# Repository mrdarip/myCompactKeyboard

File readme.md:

# my compact keyboard

## Description

## PCB
Here are pictures of my pcb:

| **Schematic** | **PCB** |
|---------------|---------|
|||

Hope it looks good to you!

[x] I ran DRC and there are 0 errors

## CAD
Designed two using OpenSCAD! I edited my previous macropad case for the keyboard

It's made to be 3D printed, and as it doesn't need supports nor any post processing, mass produce.

## Firmware

I wrote the firmware using kmk, you can see it inside the repo. It's pretty simple, but I'm proud of it!

## BOM
| **Quantity** | **Item**                          |
|--------------|-----------------------------------|
| 1            | Raspberry Pi Pico                |
| 91          | Switches                         |
| 3           | Hotwap sockets                   |
| 96           | 1N4148 diodes                    |
| 96           | LED_WS2812B                      |
| 1            | Audio Jack 4                     |
| 1            | SSD1306                          |
| 2            | Rotary encoder                   |
| 1           | keycaps set                        |
| 3            | stabilizers set                      |
| 9            | bolts and nuts                 |

## IMPORTANT

- Dont send the 3d printed case  
    I'll print it myself so I'll get less customs fees.
- Don't send the soldering iron  
  I have one, less electronics waste, less customs fees.

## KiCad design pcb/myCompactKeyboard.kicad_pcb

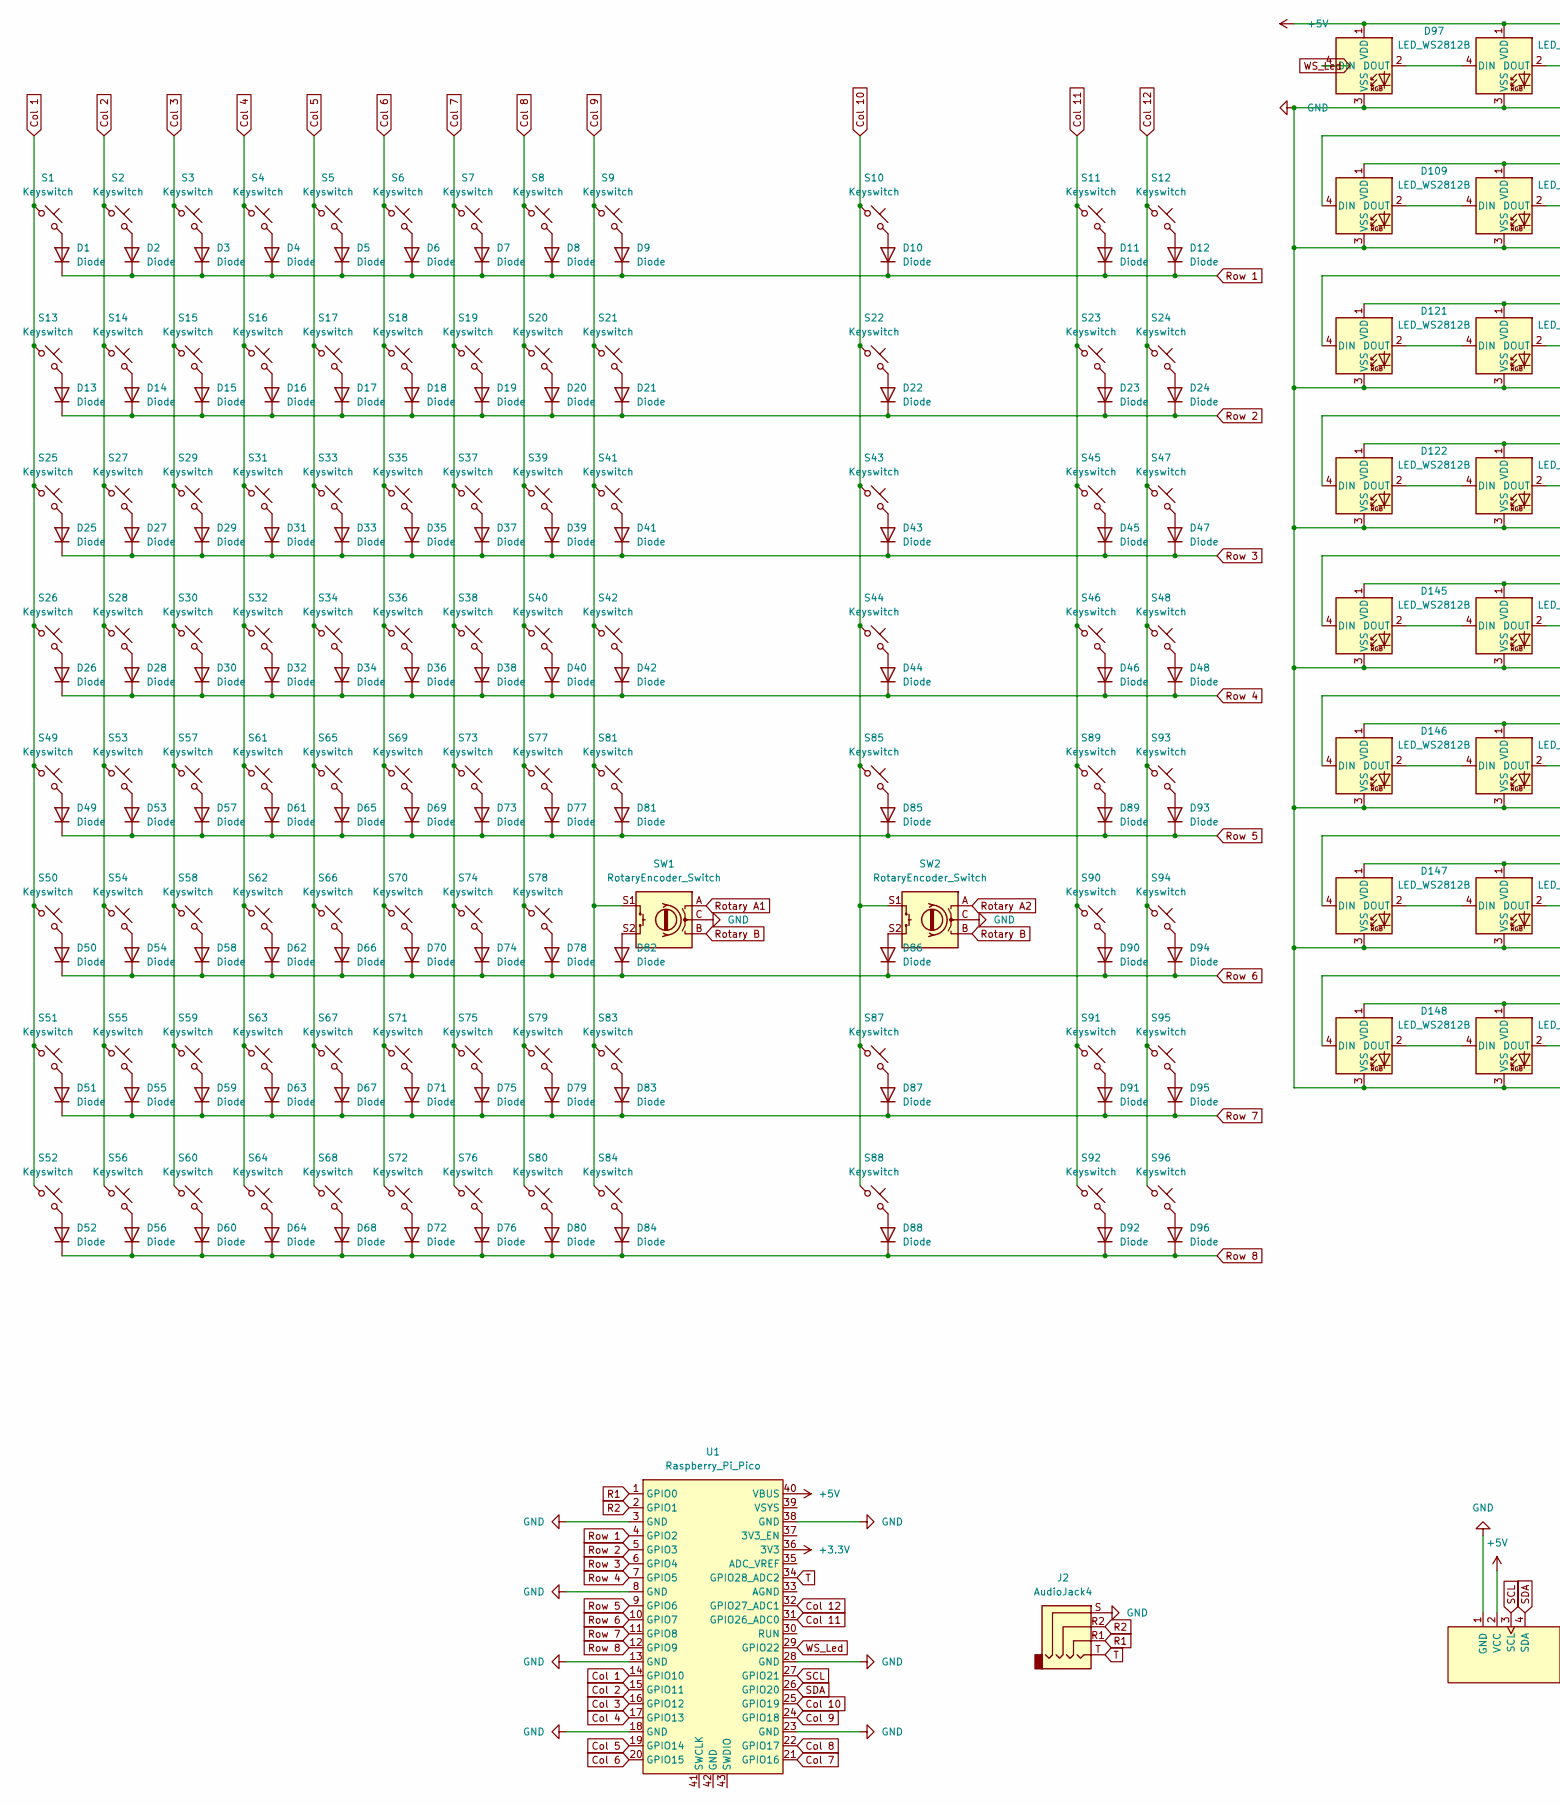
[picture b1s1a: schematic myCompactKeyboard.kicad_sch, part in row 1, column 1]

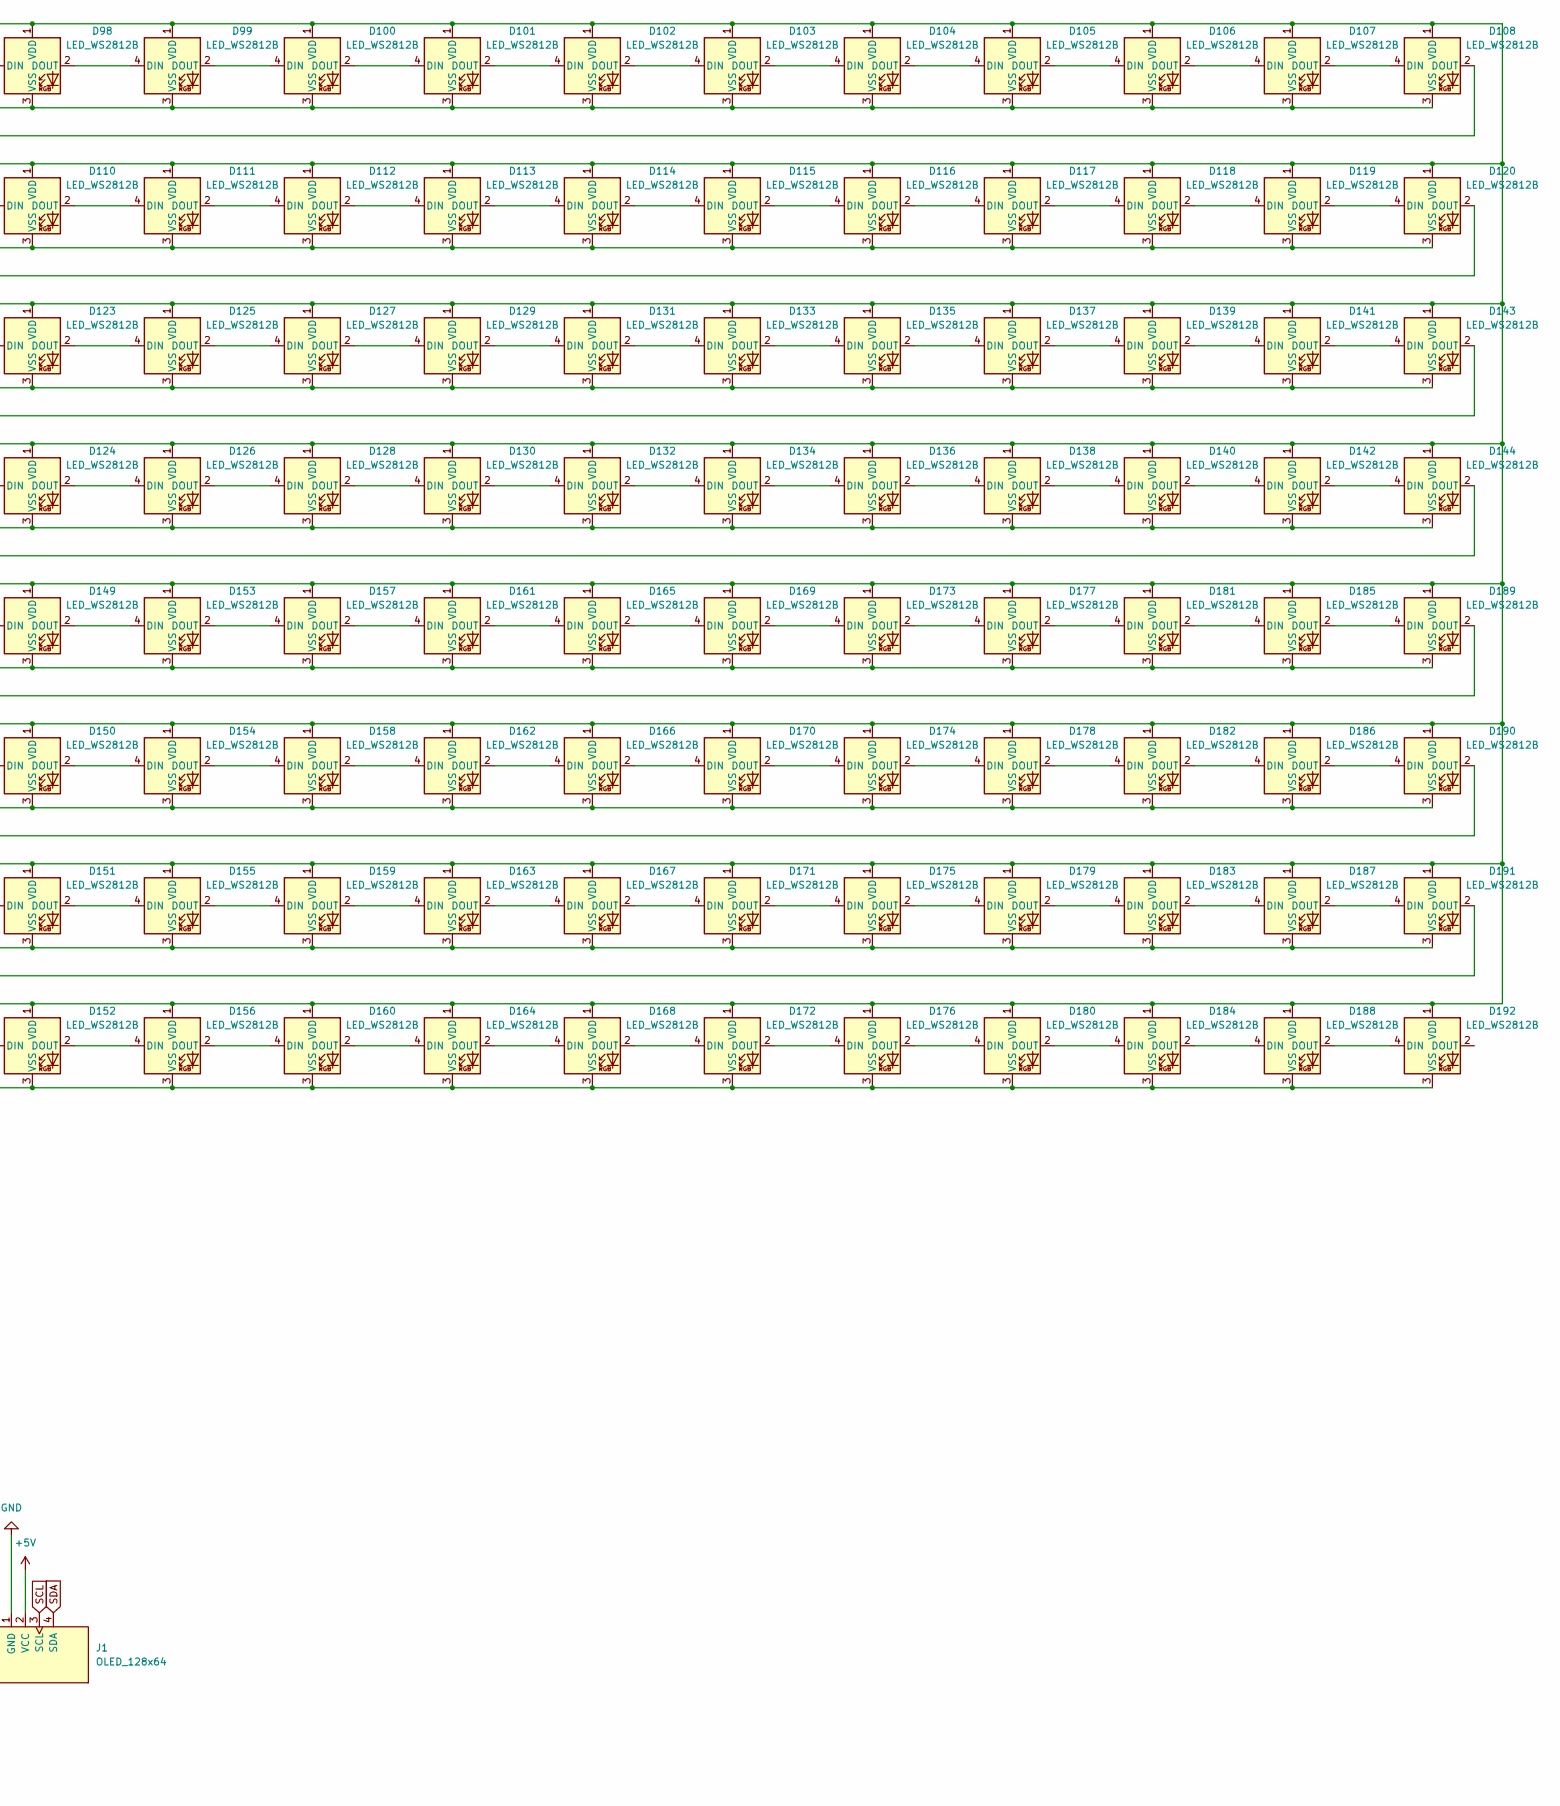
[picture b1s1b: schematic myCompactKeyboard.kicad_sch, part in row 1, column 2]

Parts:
D1, D2, D3, D4, D5, D6, D7, D8, D9, D10, D11, D12, D13, D14, D15, D16, D17, D18, D19, D20, D21, D22, D23, D24, D25, D26, D27, D28, D29, D30, D31, D32, D33, D34, D35, D36, D37, D38, D39, D40, D41, D42, D43, D44, D45, D46, D47, D48, D49, D50, D51, D52, D53, D54, D55, D56, D57, D58, D59, D60, D61, D62, D63, D64, D65, D66, D67, D68, D69, D70, D71, D72, D73, D74, D75, D76, D77, D78, D79, D80, D81, D82, D83, D84, D85, D86, D87, D88, D89, D90, D91, D92, D93, D94, D95, D96: Diode; Diode_DO-35
D97, D98, D99, D100, D101, D102, D103, D104, D105, D106, D107, D108, D109, D110, D111, D112, D113, D114, D115, D116, D117, D118, D119, D120, D121, D122, D123, D124, D125, D126, D127, D128, D129, D130, D131, D132, D133, D134, D135, D136, D137, D138, D139, D140, D141, D142, D143, D144, D145, D146, D147, D148, D149, D150, D151, D152, D153, D154, D155, D156, D157, D158, D159, D160, D161, D162, D163, D164, D165, D166, D167, D168, D169, D170, D171, D172, D173, D174, D175, D176, D177, D178, D179, D180, D181, D182, D183, D184, D185, D186, D187, D188, D189, D190, D191, D192: LED_WS2812B; SK6812MINI-E
J1: OLED_128x64
J2: AudioJack4; Jack_3.5mm_CUI_SJ1-3524N_Horizontal
S1, S2, S3, S4, S5, S6, S7, S8, S9, S10, S11, S12, S13, S14, S15, S16, S17, S18, S19, S20, S21, S22, S23, S24, S25, S26, S27, S28, S29, S30, S31, S32, S33, S34, S35, S36, S37, S38, S39, S40, S41, S42, S43, S44, S45, S46, S47, S48, S49, S50, S51, S52, S53, S54, S55, S56, S57, S58, S59, S60, S61, S62, S63, S64, S65, S66, S67, S68, S69, S70, S71, S72, S73, S74, S75, S76, S77, S78, S79, S80, S81, S83, S84, S85, S87, S88, S89, S90, S91, S92, S93, S94, S95, S96: Keyswitch; MX_PCB_1.00u
SW1, SW2: RotaryEncoder_Switch; RotaryEncoder_Alps_EC11E-Switch_Vertical_H20mm
U1: Raspberry_Pi_Pico

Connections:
+3.3V: U1.36 (3V3)
+5V: D97.1 (VDD), D98.1 (VDD), D99.1 (VDD), D100.1 (VDD), D101.1 (VDD), D102.1 (VDD), D103.1 (VDD), D104.1 (VDD), D105.1 (VDD), D106.1 (VDD), D107.1 (VDD), D108.1 (VDD), D109.1 (VDD), D110.1 (VDD), D111.1 (VDD), D112.1 (VDD), D113.1 (VDD), D114.1 (VDD), D115.1 (VDD), D116.1 (VDD), D117.1 (VDD), D118.1 (VDD), D119.1 (VDD), D120.1 (VDD), D121.1 (VDD), D122.1 (VDD), D123.1 (VDD), D124.1 (VDD), D125.1 (VDD), D126.1 (VDD), D127.1 (VDD), D128.1 (VDD), D129.1 (VDD), D130.1 (VDD), D131.1 (VDD), D132.1 (VDD), D133.1 (VDD), D134.1 (VDD), D135.1 (VDD), D136.1 (VDD), D137.1 (VDD), D138.1 (VDD), D139.1 (VDD), D140.1 (VDD), D141.1 (VDD), D142.1 (VDD), D143.1 (VDD), D144.1 (VDD), D145.1 (VDD), D146.1 (VDD), D147.1 (VDD), D148.1 (VDD), D149.1 (VDD), D150.1 (VDD), D151.1 (VDD), D152.1 (VDD), D153.1 (VDD), D154.1 (VDD), D155.1 (VDD), D156.1 (VDD), D157.1 (VDD), D158.1 (VDD), D159.1 (VDD), D160.1 (VDD), D161.1 (VDD), D162.1 (VDD), D163.1 (VDD), D164.1 (VDD), D165.1 (VDD), D166.1 (VDD), D167.1 (VDD), D168.1 (VDD), D169.1 (VDD), D170.1 (VDD), D171.1 (VDD), D172.1 (VDD), D173.1 (VDD), D174.1 (VDD), D175.1 (VDD), D176.1 (VDD), D177.1 (VDD), D178.1 (VDD), D179.1 (VDD), D180.1 (VDD), D181.1 (VDD), D182.1 (VDD), D183.1 (VDD), D184.1 (VDD), D185.1 (VDD), D186.1 (VDD), D187.1 (VDD), D188.1 (VDD), D189.1 (VDD), D190.1 (VDD), D191.1 (VDD), D192.1 (VDD), J1.2 (VCC), U1.40 (VBUS)
Col 1: S1.1, S13.1, S25.1, S26.1, S49.1, S50.1, S51.1, S52.1, U1.14 (GPIO10)
Col 2: S2.1, S14.1, S27.1, S28.1, S53.1, S54.1, S55.1, S56.1, U1.15 (GPIO11)
Col 3: S3.1, S15.1, S29.1, S30.1, S57.1, S58.1, S59.1, S60.1, U1.16 (GPIO12)
Col 4: S4.1, S16.1, S31.1, S32.1, S61.1, S62.1, S63.1, S64.1, U1.17 (GPIO13)
Col 5: S5.1, S17.1, S33.1, S34.1, S65.1, S66.1, S67.1, S68.1, U1.19 (GPIO14)
Col 6: S6.1, S18.1, S35.1, S36.1, S69.1, S70.1, S71.1, S72.1, U1.20 (GPIO15)
Col 7: S7.1, S19.1, S37.1, S38.1, S73.1, S74.1, S75.1, S76.1, U1.21 (GPIO16)
Col 8: S8.1, S20.1, S39.1, S40.1, S77.1, S78.1, S79.1, S80.1, U1.22 (GPIO17)
Col 9: S9.1, S21.1, S41.1, S42.1, S81.1, S83.1, S84.1, SW1.S1, U1.24 (GPIO18)
Col 10: S10.1, S22.1, S43.1, S44.1, S85.1, S87.1, S88.1, SW2.S1, U1.25 (GPIO19)
Col 11: S11.1, S23.1, S45.1, S46.1, S89.1, S90.1, S91.1, S92.1, U1.31 (GPIO26_ADC0)
Col 12: S12.1, S24.1, S47.1, S48.1, S93.1, S94.1, S95.1, S96.1, U1.32 (GPIO27_ADC1)
GND: D97.3 (VSS), D98.3 (VSS), D99.3 (VSS), D100.3 (VSS), D101.3 (VSS), D102.3 (VSS), D103.3 (VSS), D104.3 (VSS), D105.3 (VSS), D106.3 (VSS), D107.3 (VSS), D108.3 (VSS), D109.3 (VSS), D110.3 (VSS), D111.3 (VSS), D112.3 (VSS), D113.3 (VSS), D114.3 (VSS), D115.3 (VSS), D116.3 (VSS), D117.3 (VSS), D118.3 (VSS), D119.3 (VSS), D120.3 (VSS), D121.3 (VSS), D122.3 (VSS), D123.3 (VSS), D124.3 (VSS), D125.3 (VSS), D126.3 (VSS), D127.3 (VSS), D128.3 (VSS), D129.3 (VSS), D130.3 (VSS), D131.3 (VSS), D132.3 (VSS), D133.3 (VSS), D134.3 (VSS), D135.3 (VSS), D136.3 (VSS), D137.3 (VSS), D138.3 (VSS), D139.3 (VSS), D140.3 (VSS), D141.3 (VSS), D142.3 (VSS), D143.3 (VSS), D144.3 (VSS), D145.3 (VSS), D146.3 (VSS), D147.3 (VSS), D148.3 (VSS), D149.3 (VSS), D150.3 (VSS), D151.3 (VSS), D152.3 (VSS), D153.3 (VSS), D154.3 (VSS), D155.3 (VSS), D156.3 (VSS), D157.3 (VSS), D158.3 (VSS), D159.3 (VSS), D160.3 (VSS), D161.3 (VSS), D162.3 (VSS), D163.3 (VSS), D164.3 (VSS), D165.3 (VSS), D166.3 (VSS), D167.3 (VSS), D168.3 (VSS), D169.3 (VSS), D170.3 (VSS), D171.3 (VSS), D172.3 (VSS), D173.3 (VSS), D174.3 (VSS), D175.3 (VSS), D176.3 (VSS), D177.3 (VSS), D178.3 (VSS), D179.3 (VSS), D180.3 (VSS), D181.3 (VSS), D182.3 (VSS), D183.3 (VSS), D184.3 (VSS), D185.3 (VSS), D186.3 (VSS), D187.3 (VSS), D188.3 (VSS), D189.3 (VSS), D190.3 (VSS), D191.3 (VSS), D192.3 (VSS), J1.1 (GND), J2.S, SW1.C, SW2.C, U1.3 (GND), U1.8 (GND), U1.13 (GND), U1.18 (GND), U1.23 (GND), U1.28 (GND), U1.38 (GND)
unnamed: D1.2 (A), S1.2
unnamed: D2.2 (A), S2.2
unnamed: D3.2 (A), S3.2
unnamed: D4.2 (A), S4.2
unnamed: D5.2 (A), S5.2
unnamed: D6.2 (A), S6.2
unnamed: D7.2 (A), S7.2
unnamed: D8.2 (A), S8.2
unnamed: D9.2 (A), S9.2
unnamed: D10.2 (A), S10.2
unnamed: D11.2 (A), S11.2
unnamed: D12.2 (A), S12.2
unnamed: D13.2 (A), S13.2
unnamed: D14.2 (A), S14.2
unnamed: D15.2 (A), S15.2
unnamed: D16.2 (A), S16.2
unnamed: D17.2 (A), S17.2
unnamed: D18.2 (A), S18.2
unnamed: D19.2 (A), S19.2
unnamed: D20.2 (A), S20.2
unnamed: D21.2 (A), S21.2
unnamed: D22.2 (A), S22.2
unnamed: D23.2 (A), S23.2
unnamed: D24.2 (A), S24.2
unnamed: D25.2 (A), S25.2
unnamed: D26.2 (A), S26.2
unnamed: D27.2 (A), S27.2
unnamed: D28.2 (A), S28.2
unnamed: D29.2 (A), S29.2
unnamed: D30.2 (A), S30.2
unnamed: D31.2 (A), S31.2
unnamed: D32.2 (A), S32.2
unnamed: D33.2 (A), S33.2
unnamed: D34.2 (A), S34.2
unnamed: D35.2 (A), S35.2
unnamed: D36.2 (A), S36.2
unnamed: D37.2 (A), S37.2
unnamed: D38.2 (A), S38.2
unnamed: D39.2 (A), S39.2
unnamed: D40.2 (A), S40.2
unnamed: D41.2 (A), S41.2
unnamed: D42.2 (A), S42.2
unnamed: D43.2 (A), S43.2
unnamed: D44.2 (A), S44.2
unnamed: D45.2 (A), S45.2
unnamed: D46.2 (A), S46.2
unnamed: D47.2 (A), S47.2
unnamed: D48.2 (A), S48.2
unnamed: D49.2 (A), S49.2
unnamed: D50.2 (A), S50.2
unnamed: D51.2 (A), S51.2
unnamed: D52.2 (A), S52.2
unnamed: D53.2 (A), S53.2
unnamed: D54.2 (A), S54.2
unnamed: D55.2 (A), S55.2
unnamed: D56.2 (A), S56.2
unnamed: D57.2 (A), S57.2
unnamed: D58.2 (A), S58.2
unnamed: D59.2 (A), S59.2
unnamed: D60.2 (A), S60.2
unnamed: D61.2 (A), S61.2
unnamed: D62.2 (A), S62.2
unnamed: D63.2 (A), S63.2
unnamed: D64.2 (A), S64.2
unnamed: D65.2 (A), S65.2
unnamed: D66.2 (A), S66.2
unnamed: D67.2 (A), S67.2
unnamed: D68.2 (A), S68.2
unnamed: D69.2 (A), S69.2
unnamed: D70.2 (A), S70.2
unnamed: D71.2 (A), S71.2
unnamed: D72.2 (A), S72.2
unnamed: D73.2 (A), S73.2
unnamed: D74.2 (A), S74.2
unnamed: D75.2 (A), S75.2
unnamed: D76.2 (A), S76.2
unnamed: D77.2 (A), S77.2
unnamed: D78.2 (A), S78.2
unnamed: D79.2 (A), S79.2
unnamed: D80.2 (A), S80.2
unnamed: D81.2 (A), S81.2
unnamed: D82.2 (A), SW1.S2
unnamed: D83.2 (A), S83.2
unnamed: D84.2 (A), S84.2
unnamed: D85.2 (A), S85.2
unnamed: D86.2 (A), SW2.S2
unnamed: D87.2 (A), S87.2
unnamed: D88.2 (A), S88.2
unnamed: D89.2 (A), S89.2
unnamed: D90.2 (A), S90.2
unnamed: D91.2 (A), S91.2
unnamed: D92.2 (A), S92.2
unnamed: D93.2 (A), S93.2
unnamed: D94.2 (A), S94.2
unnamed: D95.2 (A), S95.2
unnamed: D96.2 (A), S96.2
unnamed: D97.2 (DOUT), D98.4 (DIN)
unnamed: D98.2 (DOUT), D99.4 (DIN)
unnamed: D99.2 (DOUT), D100.4 (DIN)
unnamed: D100.2 (DOUT), D101.4 (DIN)
unnamed: D101.2 (DOUT), D102.4 (DIN)
unnamed: D102.2 (DOUT), D103.4 (DIN)
unnamed: D103.2 (DOUT), D104.4 (DIN)
unnamed: D104.2 (DOUT), D105.4 (DIN)
unnamed: D105.2 (DOUT), D106.4 (DIN)
unnamed: D106.2 (DOUT), D107.4 (DIN)
unnamed: D107.2 (DOUT), D108.4 (DIN)
unnamed: D108.2 (DOUT), D109.4 (DIN)
unnamed: D109.2 (DOUT), D110.4 (DIN)
unnamed: D110.2 (DOUT), D111.4 (DIN)
unnamed: D111.2 (DOUT), D112.4 (DIN)
unnamed: D112.2 (DOUT), D113.4 (DIN)
unnamed: D113.2 (DOUT), D114.4 (DIN)
unnamed: D114.2 (DOUT), D115.4 (DIN)
unnamed: D115.2 (DOUT), D116.4 (DIN)
unnamed: D116.2 (DOUT), D117.4 (DIN)
unnamed: D117.2 (DOUT), D118.4 (DIN)
unnamed: D118.2 (DOUT), D119.4 (DIN)
unnamed: D119.2 (DOUT), D120.4 (DIN)
unnamed: D120.2 (DOUT), D121.4 (DIN)
unnamed: D121.2 (DOUT), D123.4 (DIN)
unnamed: D122.4 (DIN), D143.2 (DOUT)
unnamed: D122.2 (DOUT), D124.4 (DIN)
unnamed: D123.2 (DOUT), D125.4 (DIN)
unnamed: D124.2 (DOUT), D126.4 (DIN)
unnamed: D125.2 (DOUT), D127.4 (DIN)
unnamed: D126.2 (DOUT), D128.4 (DIN)
unnamed: D127.2 (DOUT), D129.4 (DIN)
unnamed: D128.2 (DOUT), D130.4 (DIN)
unnamed: D129.2 (DOUT), D131.4 (DIN)
unnamed: D130.2 (DOUT), D132.4 (DIN)
unnamed: D131.2 (DOUT), D133.4 (DIN)
unnamed: D132.2 (DOUT), D134.4 (DIN)
unnamed: D133.2 (DOUT), D135.4 (DIN)
unnamed: D134.2 (DOUT), D136.4 (DIN)
unnamed: D135.2 (DOUT), D137.4 (DIN)
unnamed: D136.2 (DOUT), D138.4 (DIN)
unnamed: D137.2 (DOUT), D139.4 (DIN)
unnamed: D138.2 (DOUT), D140.4 (DIN)
unnamed: D139.2 (DOUT), D141.4 (DIN)
unnamed: D140.2 (DOUT), D142.4 (DIN)
unnamed: D141.2 (DOUT), D143.4 (DIN)
unnamed: D142.2 (DOUT), D144.4 (DIN)
unnamed: D144.2 (DOUT), D145.4 (DIN)
unnamed: D145.2 (DOUT), D149.4 (DIN)
unnamed: D146.4 (DIN), D189.2 (DOUT)
unnamed: D146.2 (DOUT), D150.4 (DIN)
unnamed: D147.4 (DIN), D190.2 (DOUT)
unnamed: D147.2 (DOUT), D151.4 (DIN)
unnamed: D148.4 (DIN), D191.2 (DOUT)
unnamed: D148.2 (DOUT), D152.4 (DIN)
unnamed: D149.2 (DOUT), D153.4 (DIN)
unnamed: D150.2 (DOUT), D154.4 (DIN)
unnamed: D151.2 (DOUT), D155.4 (DIN)
unnamed: D152.2 (DOUT), D156.4 (DIN)
unnamed: D153.2 (DOUT), D157.4 (DIN)
unnamed: D154.2 (DOUT), D158.4 (DIN)
unnamed: D155.2 (DOUT), D159.4 (DIN)
unnamed: D156.2 (DOUT), D160.4 (DIN)
unnamed: D157.2 (DOUT), D161.4 (DIN)
unnamed: D158.2 (DOUT), D162.4 (DIN)
unnamed: D159.2 (DOUT), D163.4 (DIN)
unnamed: D160.2 (DOUT), D164.4 (DIN)
unnamed: D161.2 (DOUT), D165.4 (DIN)
unnamed: D162.2 (DOUT), D166.4 (DIN)
unnamed: D163.2 (DOUT), D167.4 (DIN)
unnamed: D164.2 (DOUT), D168.4 (DIN)
unnamed: D165.2 (DOUT), D169.4 (DIN)
unnamed: D166.2 (DOUT), D170.4 (DIN)
unnamed: D167.2 (DOUT), D171.4 (DIN)
unnamed: D168.2 (DOUT), D172.4 (DIN)
unnamed: D169.2 (DOUT), D173.4 (DIN)
unnamed: D170.2 (DOUT), D174.4 (DIN)
unnamed: D171.2 (DOUT), D175.4 (DIN)
unnamed: D172.2 (DOUT), D176.4 (DIN)
unnamed: D173.2 (DOUT), D177.4 (DIN)
unnamed: D174.2 (DOUT), D178.4 (DIN)
unnamed: D175.2 (DOUT), D179.4 (DIN)
unnamed: D176.2 (DOUT), D180.4 (DIN)
unnamed: D177.2 (DOUT), D181.4 (DIN)
unnamed: D178.2 (DOUT), D182.4 (DIN)
unnamed: D179.2 (DOUT), D183.4 (DIN)
unnamed: D180.2 (DOUT), D184.4 (DIN)
unnamed: D181.2 (DOUT), D185.4 (DIN)
unnamed: D182.2 (DOUT), D186.4 (DIN)
unnamed: D183.2 (DOUT), D187.4 (DIN)
unnamed: D184.2 (DOUT), D188.4 (DIN)
unnamed: D185.2 (DOUT), D189.4 (DIN)
unnamed: D186.2 (DOUT), D190.4 (DIN)
unnamed: D187.2 (DOUT), D191.4 (DIN)
unnamed: D188.2 (DOUT), D192.4 (DIN)
R1: J2.R1, U1.1 (GPIO0)
R2: J2.R2, U1.2 (GPIO1)
Rotary A1: SW1.A
Rotary A2: SW2.A
Rotary B: SW1.B, SW2.B
Row 1: D1.1 (K), D2.1 (K), D3.1 (K), D4.1 (K), D5.1 (K), D6.1 (K), D7.1 (K), D8.1 (K), D9.1 (K), D10.1 (K), D11.1 (K), D12.1 (K), U1.4 (GPIO2)
Row 2: D13.1 (K), D14.1 (K), D15.1 (K), D16.1 (K), D17.1 (K), D18.1 (K), D19.1 (K), D20.1 (K), D21.1 (K), D22.1 (K), D23.1 (K), D24.1 (K), U1.5 (GPIO3)
Row 3: D25.1 (K), D27.1 (K), D29.1 (K), D31.1 (K), D33.1 (K), D35.1 (K), D37.1 (K), D39.1 (K), D41.1 (K), D43.1 (K), D45.1 (K), D47.1 (K), U1.6 (GPIO4)
Row 4: D26.1 (K), D28.1 (K), D30.1 (K), D32.1 (K), D34.1 (K), D36.1 (K), D38.1 (K), D40.1 (K), D42.1 (K), D44.1 (K), D46.1 (K), D48.1 (K), U1.7 (GPIO5)
Row 5: D49.1 (K), D53.1 (K), D57.1 (K), D61.1 (K), D65.1 (K), D69.1 (K), D73.1 (K), D77.1 (K), D81.1 (K), D85.1 (K), D89.1 (K), D93.1 (K), U1.9 (GPIO6)
Row 6: D50.1 (K), D54.1 (K), D58.1 (K), D62.1 (K), D66.1 (K), D70.1 (K), D74.1 (K), D78.1 (K), D82.1 (K), D86.1 (K), D90.1 (K), D94.1 (K), U1.10 (GPIO7)
Row 7: D51.1 (K), D55.1 (K), D59.1 (K), D63.1 (K), D67.1 (K), D71.1 (K), D75.1 (K), D79.1 (K), D83.1 (K), D87.1 (K), D91.1 (K), D95.1 (K), U1.11 (GPIO8)
Row 8: D52.1 (K), D56.1 (K), D60.1 (K), D64.1 (K), D68.1 (K), D72.1 (K), D76.1 (K), D80.1 (K), D84.1 (K), D88.1 (K), D92.1 (K), D96.1 (K), U1.12 (GPIO9)
SCL: J1.3 (SCL), U1.27 (GPIO21)
SDA: J1.4 (SDA), U1.26 (GPIO20)
T: J2.T, U1.34 (GPIO28_ADC2)
WS_Led: D97.4 (DIN), U1.29 (GPIO22)

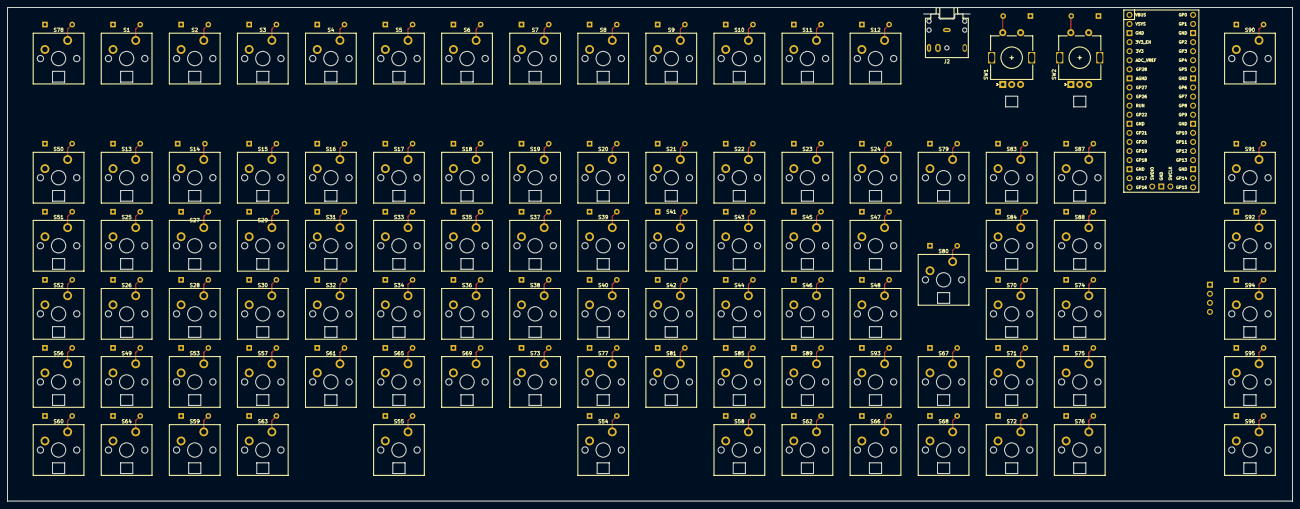
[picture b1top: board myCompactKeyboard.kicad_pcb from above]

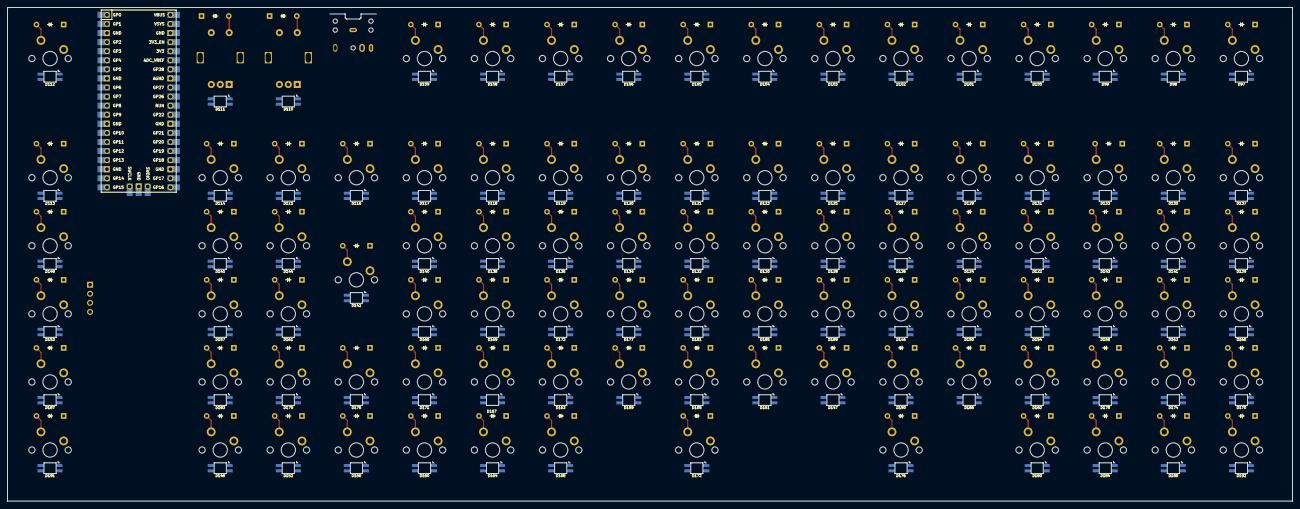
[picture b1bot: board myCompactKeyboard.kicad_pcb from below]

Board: 2 copper layers, 359.6 x 138.1 mm, 291 parts (193 on the bottom side), 218 nets.

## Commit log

2025-03-06 added initial scheme layout
2025-03-06 switched layout to 8x12
2025-03-06 added the led matrix to the schematic
2025-03-06 wired the keys in the schematic
2025-03-07 converted the light matrix to a full 12x8
2025-03-07 added labels to switch matrix
2025-03-07 added labels to rotary encoders
2025-03-07 created pcb and placed switches
2025-03-07 placed diodes on pcb
2025-03-08 placed all elements on pcb and started wiring
2025-03-08 fixed all components placement
2025-03-08 positioned all Led on the pcb
2025-03-08 flipped all diodes
2025-03-09 added a jack conector
2025-03-09 wired all simple keyswitch connections
2025-03-09 added gnd pouring
2025-03-09 wired most horizontal connections
2025-03-09 wired most easy connections
2025-03-09 wired leds and most components
2025-03-10 repositioned all leds
2025-03-11 wired most leds net
2025-03-12 completed wiring with 1 drc error
2025-03-12 changed jack to smd and fixed all errors and many warnings
2025-03-13 added x.00u switches (instead of 1.00)
2025-03-15 moved half a row down top keys
2025-03-15 fixed hotswap keys and jack
2025-03-15 converted firs spacebar to 2.75u and alt to 1.25u
2025-03-16 added submission files
2025-03-18 starte creating case in freecad
2025-03-18 created all the case "layers" in inkscape
2025-03-19 created case with svg
2025-03-23 completed and exported case
2025-03-23 remove jack and wire rotary encoders
2025-03-23 complete for the shipping
2025-03-23 add caseByLayers.3mf file
